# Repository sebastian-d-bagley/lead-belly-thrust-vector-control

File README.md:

# lead-belly-thrust-vector-control
All code, CAD, and simulation files used in creating the Lead Belly thrust vector control rocket.

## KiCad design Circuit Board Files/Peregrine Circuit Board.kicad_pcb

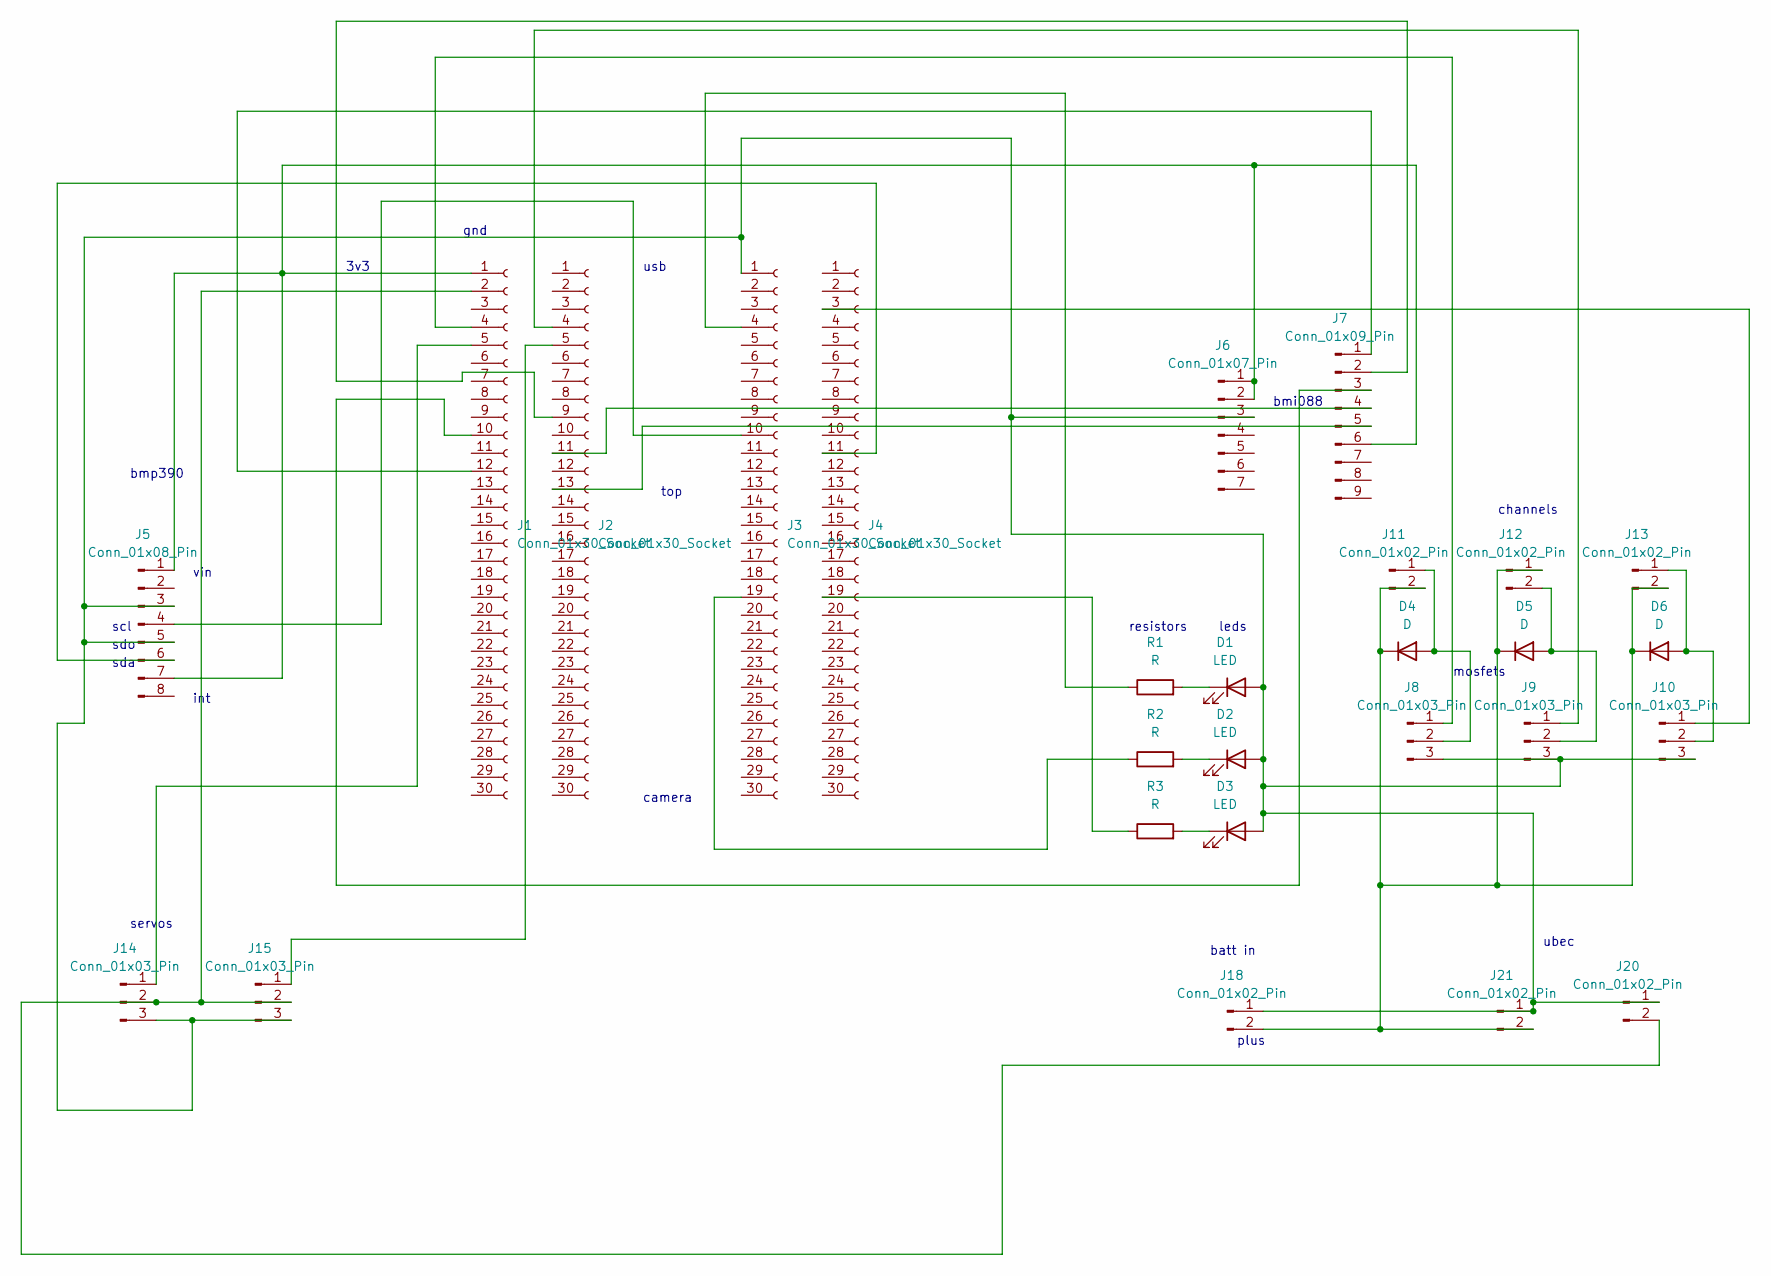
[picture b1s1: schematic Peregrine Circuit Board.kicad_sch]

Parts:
D1, D2, D3: LED; LED_D5.0mm
D4, D5, D6: D; D_5W_P12.70mm_Horizontal
J1, J2, J3, J4: Conn_01x30_Socket; PinSocket_1x30_P2.54mm_Vertical
J5: Conn_01x08_Pin; PinHeader_1x08_P2.54mm_Vertical
J6: Conn_01x07_Pin; PinHeader_1x07_P1.27mm_Vertical
J7: Conn_01x09_Pin; PinHeader_1x09_P1.27mm_Vertical
J8, J9, J10: Conn_01x03_Pin; PinHeader_1x03_P2.54mm_Vertical
J11, J12, J13: Conn_01x02_Pin; JST_EH_B2B-EH-A_1x02_P2.50mm_Vertical
J14, J15: Conn_01x03_Pin; JST_EH_B3B-EH-A_1x03_P2.50mm_Vertical
J18, J21: Conn_01x02_Pin; TerminalBlock_Altech_AK300-2_P5.00mm
J20: Conn_01x02_Pin; PinSocket_1x02_P2.54mm_Vertical
R1, R2, R3: R; R_Axial_DIN0411_L9.9mm_D3.6mm_P12.70mm_Horizontal

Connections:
unnamed: D1.2 (A), D2.2 (A), D3.2 (A), J3.1, J5.3, J5.5, J6.3, J8.3, J9.3, J10.3, J14.3, J15.3, J18.1, J20.1, J21.1
unnamed: D1.1 (K), R1.2
unnamed: D2.1 (K), R2.2
unnamed: D3.1 (K), R3.2
unnamed: D4.2 (A), J8.2, J11.1
unnamed: D4.1 (K), D5.1 (K), D6.1 (K), J11.2, J12.1, J13.2, J18.2, J21.2
unnamed: D5.2 (A), J9.2, J12.2
unnamed: D6.2 (A), J10.2, J13.1
unnamed: J1.1, J5.1, J5.7, J6.1, J6.2, J7.6
unnamed: J1.2, J14.2, J15.2, J20.2
unnamed: J1.4, J8.1
unnamed: J1.5, J14.1
unnamed: J1.10, J7.3
unnamed: J1.12, J7.1
unnamed: J2.4, J9.1
unnamed: J2.9, J7.2
unnamed: J2.11, J7.4
unnamed: J2.13, J7.5
unnamed: J3.4, R1.1
unnamed: J3.10, J5.4
unnamed: J3.19, R2.1
unnamed: J4.11, J5.6
unnamed: J4.19, R3.1
unnamed: J4.3, J10.1
unnamed: J2.5, J15.1

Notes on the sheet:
usb
int
channels
bmi088
sdo
scl
3v3
camera
servos
plus
ubec
leds
sda
bmp390
mosfets
resistors
batt in
top
gnd
vin

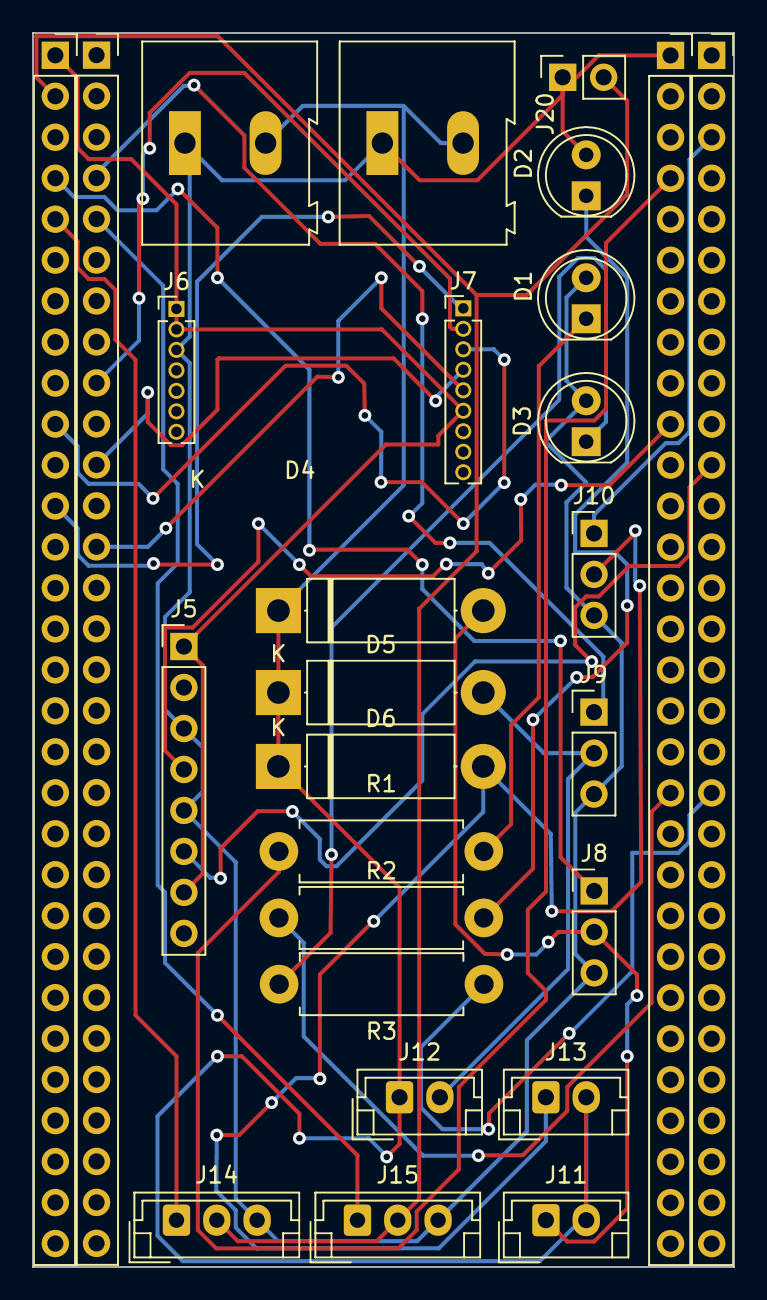
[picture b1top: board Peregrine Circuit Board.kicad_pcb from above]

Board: 2 copper layers, 43.5 x 76.5 mm, 27 parts (0 on the bottom side), 25 nets.

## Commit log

2025-10-17 Add Mount_Angle_to_Torque function for torque calculation
2025-10-17 Create folder
